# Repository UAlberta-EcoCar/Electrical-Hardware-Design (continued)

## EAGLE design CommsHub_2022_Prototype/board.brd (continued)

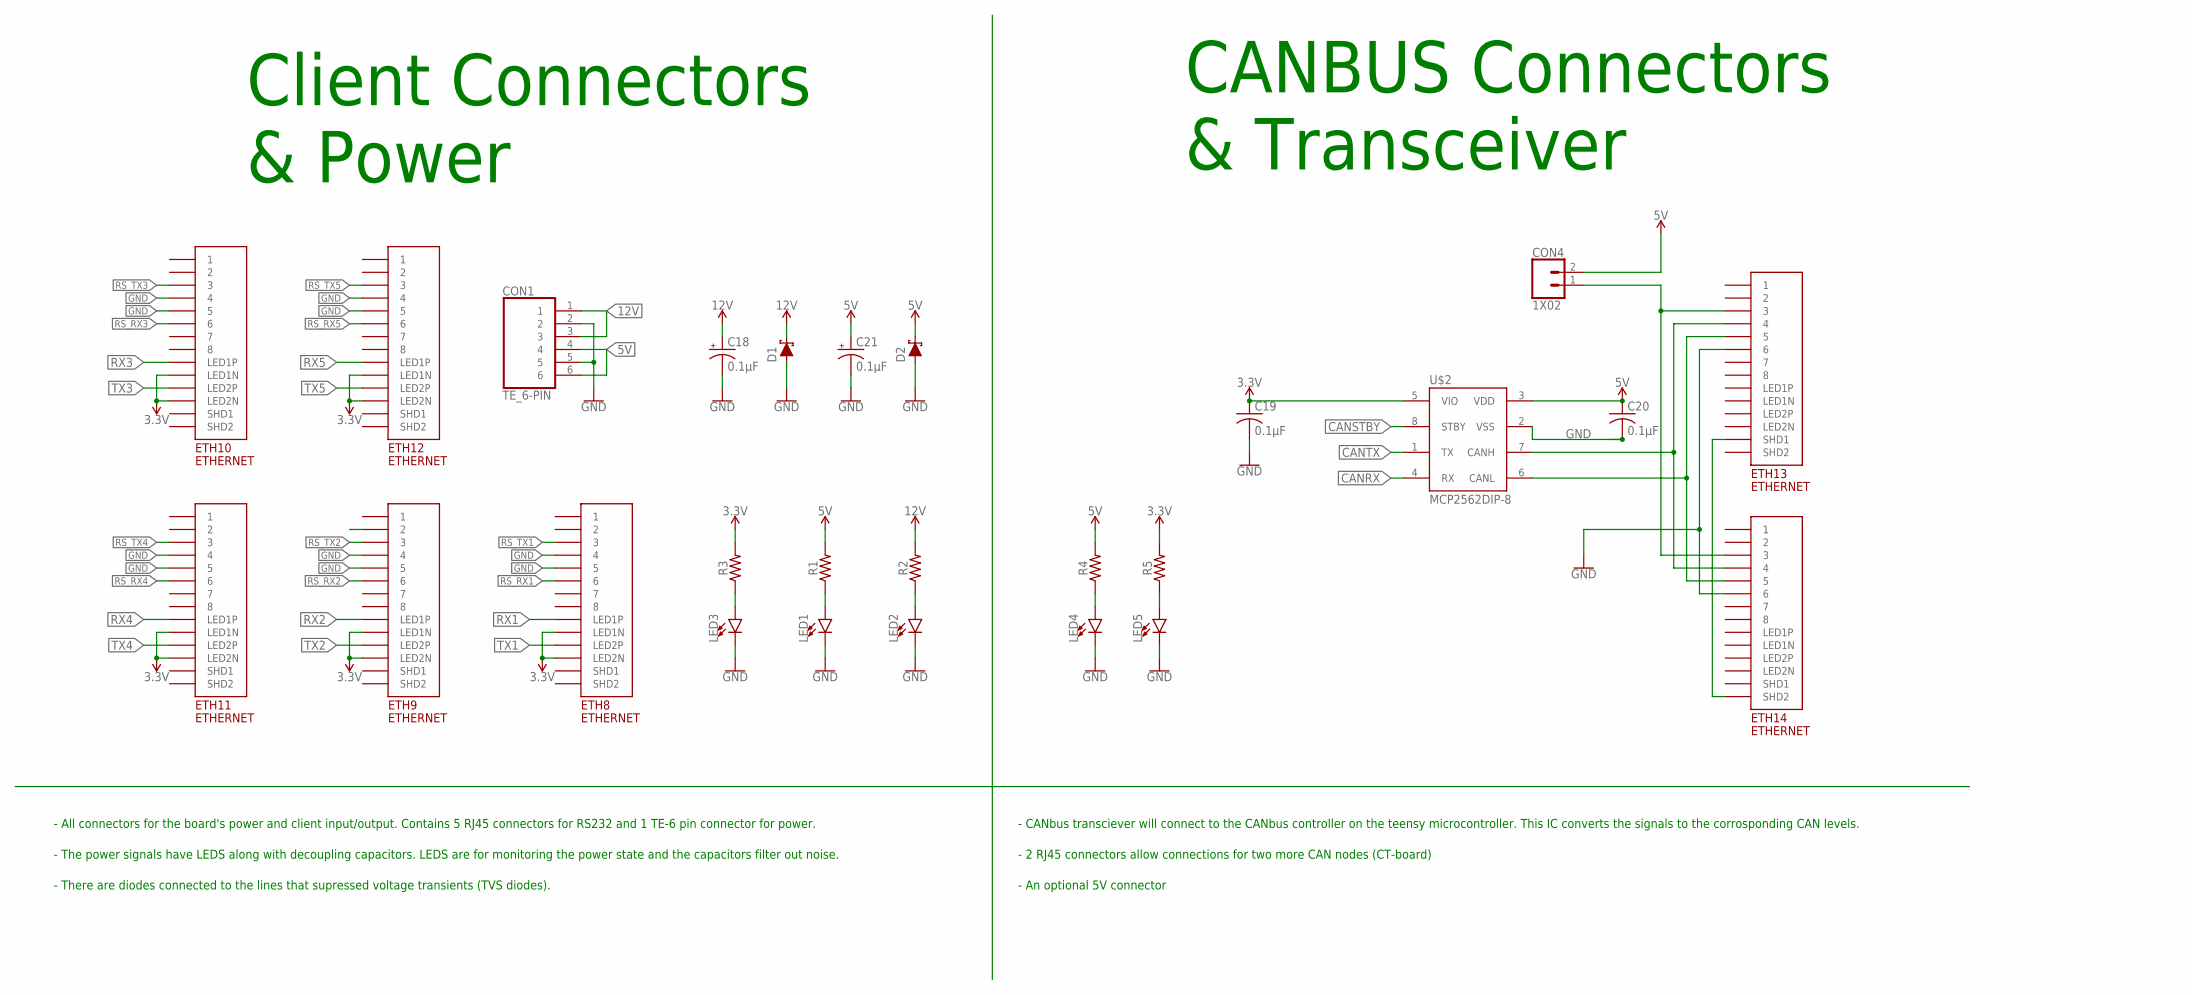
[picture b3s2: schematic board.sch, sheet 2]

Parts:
C18, C21: 0.1µF; CAPACITOR_100UF_50V
C19, C20: 0.1µF; C0805
CON1: TE_6-PIN
CON4: 1X02
D1, D2: DIODE_SCHOTTKY_DO-214AA; DO214AA
ETH8, ETH9, ETH10, ETH11, ETH12, ETH13, ETH14: ETHERNET; A122645-ND
LED1, LED2, LED3, LED4, LED5: LED_0805; 0805_LED
R1, R2, R3, R4, R5: RESISTOR_0805; 0805
U$2: MCP2562DIP-8; DIL08

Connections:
3.3V: C19.1, ETH8.P$9 (LED1N), ETH8.P$11 (LED2N), ETH9.P$9 (LED1N), ETH9.P$11 (LED2N), ETH10.P$9 (LED1N), ETH10.P$11 (LED2N), ETH11.P$9 (LED1N), ETH11.P$11 (LED2N), ETH12.P$9 (LED1N), ETH12.P$11 (LED2N), R3.2, R5.2, U$2.5 (VIO); also elsewhere on the board
5V: C20.1, C21.+, CON1.4, CON1.6, CON4.2, D2.C, R1.2, R4.2, U$2.3 (VDD)
12V: C18.+, CON1.1, CON1.3, D1.C, R2.2
CANRX: U$2.4 (RX); also elsewhere on the board
CANSTBY: U$2.8 (STBY); also elsewhere on the board
CANTX: U$2.1 (TX); also elsewhere on the board
GND: C18.-, C19.2, C20.2, C21.-, CON1.2, CON1.5, D1.A, D2.A, ETH8.P$4 (4), ETH8.P$5 (5), ETH9.P$4 (4), ETH9.P$5 (5), ETH10.P$4 (4), ETH10.P$5 (5), ETH11.P$4 (4), ETH11.P$5 (5), ETH12.P$4 (4), ETH12.P$5 (5), ETH13.P$6 (6), ETH14.P$6 (6), LED1.2 (C), LED2.2 (C), LED3.2 (C), LED4.2 (C), LED5.2 (C), U$2.2 (VSS); also elsewhere on the board
unnamed: ETH13.P$4 (4), ETH14.P$4 (4), U$2.7 (CANH)
unnamed: ETH13.P$5 (5), ETH14.P$5 (5), U$2.6 (CANL)
unnamed: CON4.1, ETH13.P$3 (3), ETH14.P$3 (3)
unnamed: ETH13.P$13 (SHD1), ETH14.P$14 (SHD2)
unnamed: LED2.1 (A), R2.1
unnamed: LED1.1 (A), R1.1
unnamed: LED3.1 (A), R3.1
unnamed: LED4.1 (A), R4.1
unnamed: LED5.1 (A), R5.1
RS_RX1: ETH8.P$6 (6); also elsewhere on the board
RS_RX2: ETH9.P$6 (6); also elsewhere on the board
RS_RX3: ETH10.P$6 (6); also elsewhere on the board
RS_RX4: ETH11.P$6 (6); also elsewhere on the board
RS_RX5: ETH12.P$6 (6); also elsewhere on the board
RS_TX1: ETH8.P$3 (3); also elsewhere on the board
RS_TX2: ETH9.P$3 (3); also elsewhere on the board
RS_TX3: ETH10.P$3 (3); also elsewhere on the board
RS_TX4: ETH11.P$3 (3); also elsewhere on the board
RS_TX5: ETH12.P$3 (3); also elsewhere on the board
RX1: ETH8.P$10 (LED1P); also elsewhere on the board
RX2: ETH9.P$10 (LED1P); also elsewhere on the board
RX3: ETH10.P$10 (LED1P); also elsewhere on the board
RX4: ETH11.P$10 (LED1P); also elsewhere on the board
RX5: ETH12.P$10 (LED1P); also elsewhere on the board
TX1: ETH8.P$12 (LED2P); also elsewhere on the board
TX2: ETH9.P$12 (LED2P); also elsewhere on the board
TX3: ETH10.P$12 (LED2P); also elsewhere on the board
TX4: ETH11.P$12 (LED2P); also elsewhere on the board
TX5: ETH12.P$12 (LED2P); also elsewhere on the board

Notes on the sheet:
Client Connectors & Power
CANBUS Connectors & Transceiver
- All connectors for the board's power and client input/output. Contains 5 RJ45 connectors for RS232 and 1 TE-6 pin connector for power. - The power signals have LEDS along with decoupling capacitors. LEDS are for monitoring the power state and the capacitors filter out noise. - There are diodes co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
- CANbus transciever will connect to the CANbus controller on the teensy microcontroller. This IC converts the signals to the corrosponding CAN levels. - 2 RJ45 connectors allow connections for two more CAN nodes (CT-board) - An optional 5V connector

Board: 2 copper layers, 46 parts (0 on the bottom side), 55 nets, no tracks yet.

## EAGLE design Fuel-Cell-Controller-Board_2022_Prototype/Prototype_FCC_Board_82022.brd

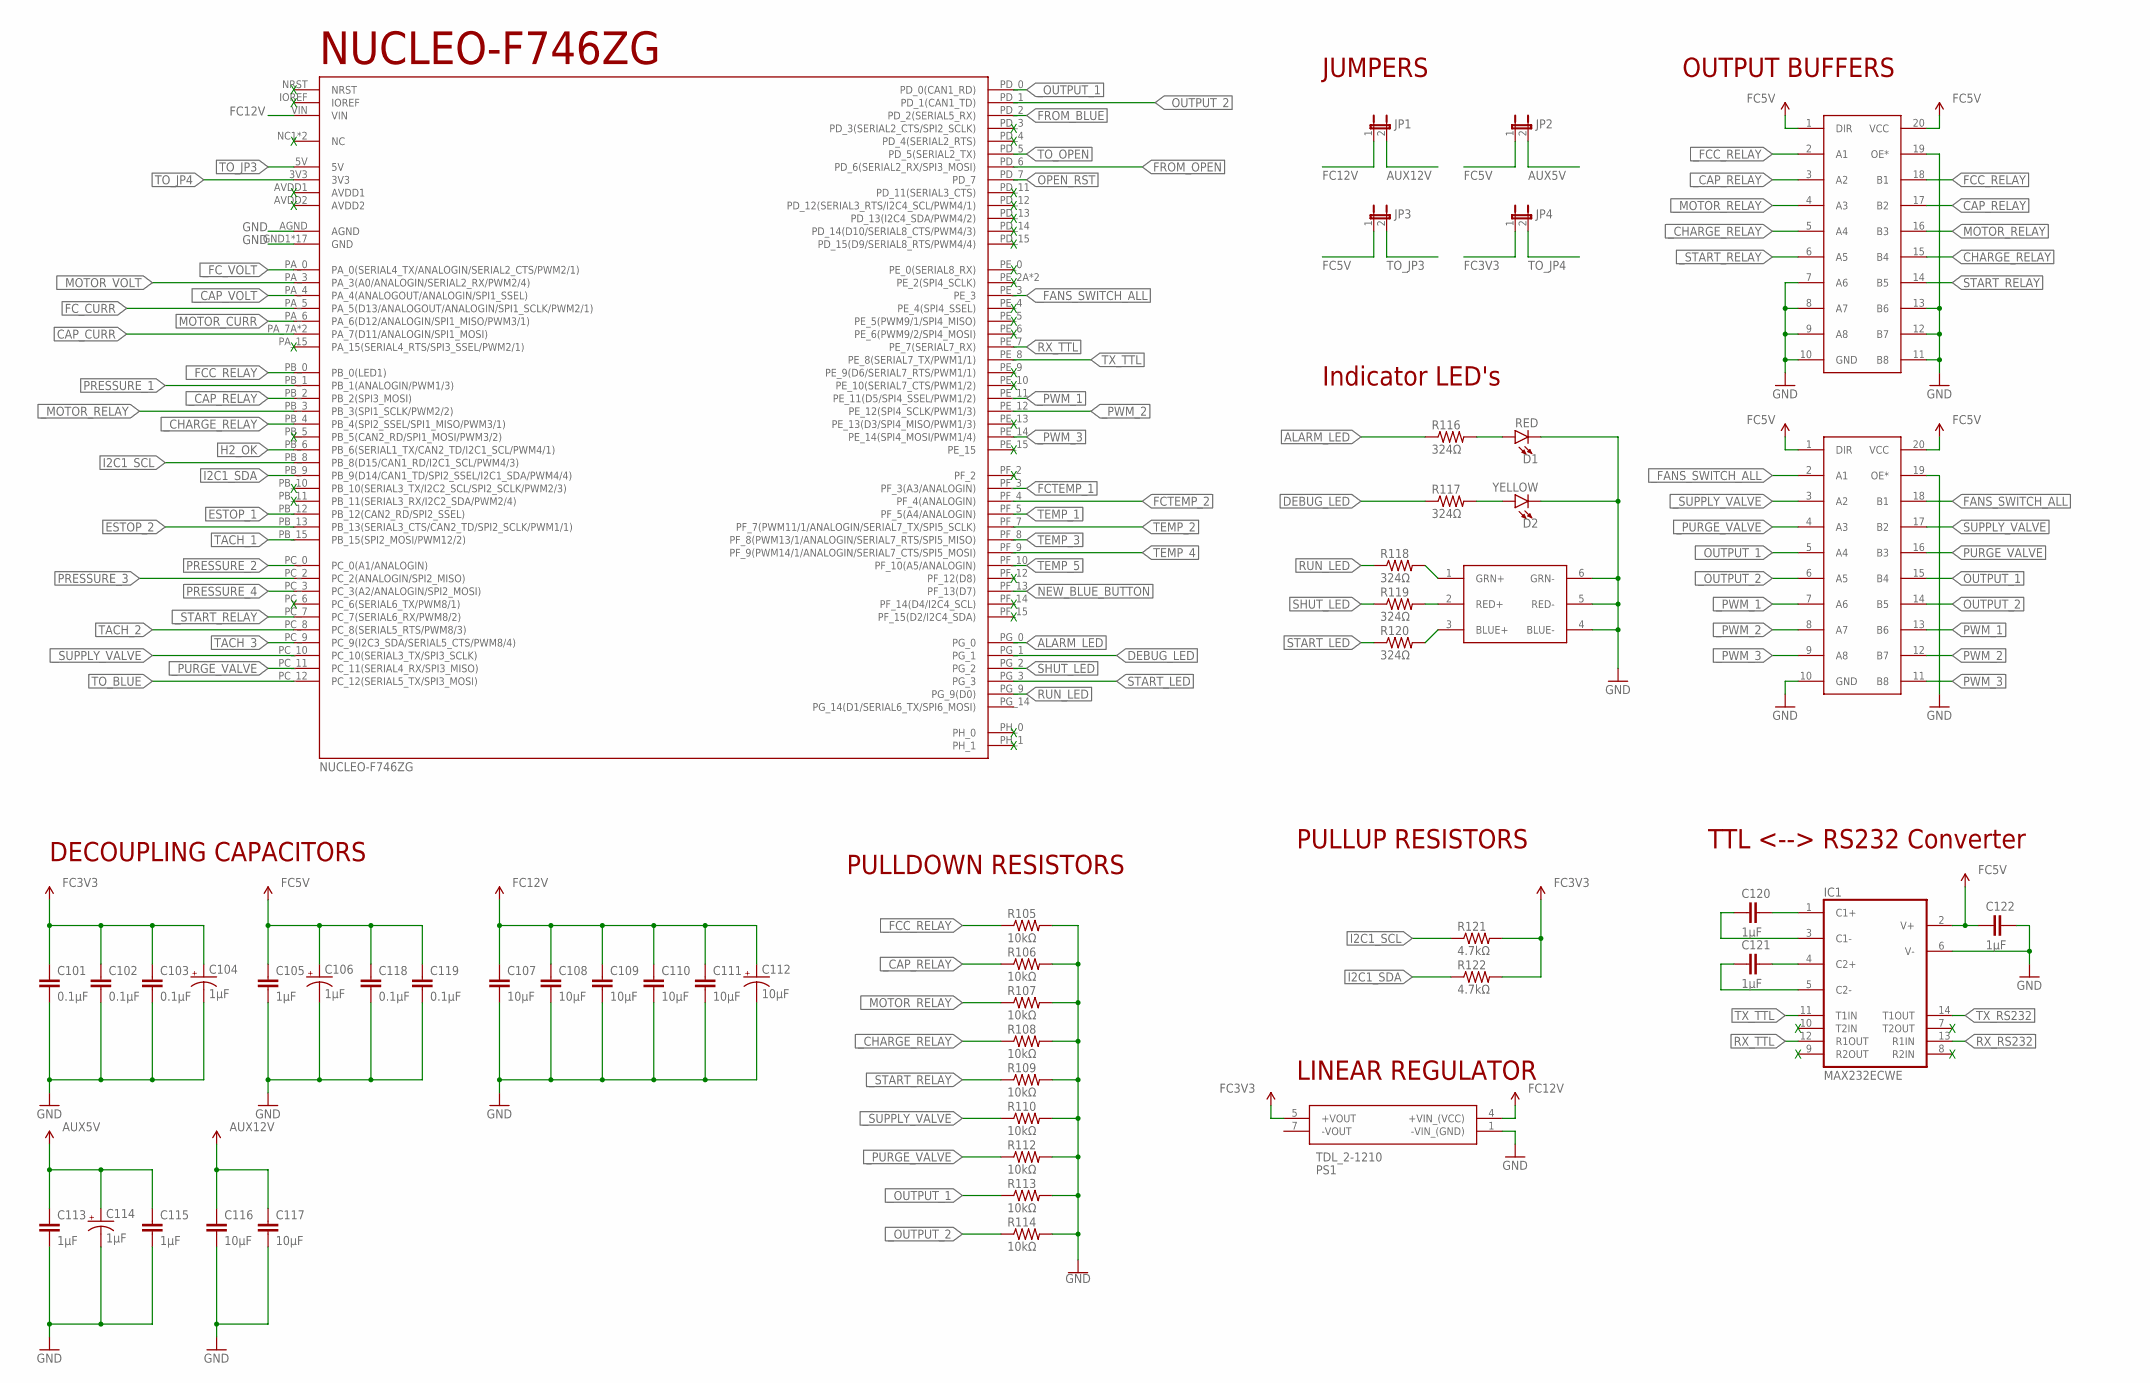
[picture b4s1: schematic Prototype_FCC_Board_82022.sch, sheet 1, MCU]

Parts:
C101, C102, C103, C118, C119: 0.1µF; 0805
C104, C106, C114: 1µF; PANASONIC_D
C105, C113, C115, C120, C121, C122: 1µF; 0805
C107, C108, C109, C110, C111, C116, C117: 10µF; 0805
C112: 10µF; PANASONIC_D
D1: RED; LED-1206
D2: YELLOW; LED-1206
IC1: MAX232ECWE; SO16L
JP1, JP2, JP3, JP4: JP1E; JP1
PS1: TDL_2-1210; TDL21210
R105, R106, R107, R108, R109, R110, R112, R113, R114: 10kΩ; 0805
R116, R117, R118, R119, R120: 324Ω; 0805
R121, R122: 4.7kΩ; 0805
U$1: NUCLEO-F746ZGNUCLEO-F746ZG; NUCLEO-F746ZG
U$3, U$5: SN74LVC245AN; DIL20
U$25: 5060BRG45060BRG4; 5060BRG4

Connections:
ALARM_LED: R116.1, U$1.PG_0
AUX5V: C113.1, C114.+, C115.1, JP2.2; also elsewhere on the board
AUX12V: C116.1, C117.1, JP1.2; also elsewhere on the board
CAP_CURR: U$1.PA_7A (PA_7(D11/ANALOGIN/SPI1_MOSI)), U$1.PA_7B (PA_7(D11/ANALOGIN/SPI1_MOSI)); also elsewhere on the board
CAP_RELAY: U$5.17 (B2); also elsewhere on the board
CHARGE_RELAY: U$5.15 (B4); also elsewhere on the board
DEBUG_LED: R117.1, U$1.PG_1
ESTOP_1: U$1.PB_12 (PB_12(CAN2_RD/SPI2_SSEL)); also elsewhere on the board
ESTOP_2: U$1.PB_13 (PB_13(SERIAL3_CTS/CAN2_TD/SPI2_SCLK/PWM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); also elsewhere on the board
FANS_SWITCH_ALL: U$3.18 (B1); also elsewhere on the board
FC12V: C107.1, C108.1, C109.1, C110.1, C111.1, C112.+, JP1.1, PS1.4 (+VIN_(VCC)), U$1.VIN; also elsewhere on the board
FCC_RELAY: U$5.18 (B1); also elsewhere on the board
FCTEMP_1: U$1.PF_3 (PF_3(A3/ANALOGIN)); also elsewhere on the board
FCTEMP_2: U$1.PF_4 (PF_4(ANALOGIN)); also elsewhere on the board
FC_CURR: U$1.PA_5 (PA_5(D13/ANALOGOUT/ANALOGIN/SPI1_SCLK/P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); also elsewhere on the board
FROM_BLUE: U$1.PD_2 (PD_2(SERIAL5_RX)); also elsewhere on the board
FROM_OPEN: U$1.PD_6 (PD_6(SERIAL2_RX/SPI3_MOSI)); also elsewhere on the board
GND: C101.2, C102.2, C103.2, C104.-, C105.2, C106.-, C107.2, C108.2, C109.2, C110.2, C111.2, C112.-, C113.2, C114.-, C115.2, C116.2, C117.2, C118.2, C119.2, C122.1, D1.C, D2.C, IC1.6 (V-), IC1.15 (GND), PS1.1 (-VIN_(GND)), R105.2, R106.2, R107.2, R108.2, R109.2, R110.2, R112.2, R113.2, R114.2, U$1.AGND, U$1.GND1 (GND), U$1.GND2 (GND), U$1.GND3 (GND), U$1.GND4 (GND), U$1.GND5 (GND), U$1.GND6 (GND), U$1.GND7 (GND), U$1.GND8 (GND), U$1.GND9 (GND), U$1.GND10 (GND), U$1.GND11 (GND), U$1.GND12 (GND), U$1.GND13 (GND), U$1.GND14 (GND), U$1.GND15 (GND), U$1.GND16 (GND), U$1.GND17 (GND), U$3.10 (GND), U$3.19 (OE*), U$5.7 (A6), U$5.8 (A7), U$5.9 (A8), U$5.10 (GND), U$5.11 (B8), U$5.12 (B7), U$5.13 (B6), U$5.19 (OE*), U$25.4 (BLUE-), U$25.5 (RED-), U$25.6 (GRN-); also elsewhere on the board
H2_OK: U$1.PB_6 (PB_6(SERIAL1_TX/CAN2_TD/I2C1_SCL/PWM4/1)); also elsewhere on the board
I2C1_SCL: R121.1, U$1.PB_8 (PB_8(D15/CAN1_RD/I2C1_SCL/PWM4/3)); also elsewhere on the board
I2C1_SDA: R122.1, U$1.PB_9 (PB_9(D14/CAN1_TD/SPI2_SSEL/I2C1_SDA/PWM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); also elsewhere on the board
MOTOR_CURR: U$1.PA_6 (PA_6(D12/ANALOGIN/SPI1_MISO/PWM3/1)); also elsewhere on the board
MOTOR_RELAY: U$5.16 (B3); also elsewhere on the board
unnamed: D1.A, R116.2
unnamed: D2.A, R117.2
unnamed: R118.2, U$25.1 (GRN+)
unnamed: R119.2, U$25.2 (RED+)
unnamed: R120.2, U$25.3 (BLUE+)
unnamed: C120.1, IC1.1 (C1+)
unnamed: C120.2, IC1.3 (C1-)
unnamed: C121.2, IC1.4 (C2+)
unnamed: C121.1, IC1.5 (C2-)
NEW_BLUE_BUTTON: U$1.PF_13 (PF_13(D7))
OPEN_RST: U$1.PD_7; also elsewhere on the board
OUTPUT_1: U$3.15 (B4); also elsewhere on the board
OUTPUT_2: U$3.14 (B5); also elsewhere on the board
PRESSURE_1: U$1.PB_1 (PB_1(ANALOGIN/PWM1/3)); also elsewhere on the board
PRESSURE_2: U$1.PC_0 (PC_0(A1/ANALOGIN)); also elsewhere on the board
PRESSURE_3: U$1.PC_2 (PC_2(ANALOGIN/SPI2_MISO)); also elsewhere on the board
PRESSURE_4: U$1.PC_3 (PC_3(A2/ANALOGIN/SPI2_MOSI)); also elsewhere on the board
PURGE_VALVE: U$3.16 (B3); also elsewhere on the board
PWM_1: U$3.13 (B6); also elsewhere on the board
PWM_2: U$3.12 (B7); also elsewhere on the board
PWM_3: U$3.11 (B8); also elsewhere on the board
RUN_LED: R118.1, U$1.PG_9 (PG_9(D0))
RX_RS232: IC1.13 (R1IN); also elsewhere on the board
RX_TTL: IC1.12 (R1OUT), U$1.PE_7 (PE_7(SERIAL7_RX))
SHUT_LED: R119.1, U$1.PG_2
START_LED: R120.1, U$1.PG_3
START_RELAY: U$5.14 (B5); also elsewhere on the board
SUPPLY_VALVE: U$3.17 (B2); also elsewhere on the board
TACH_1: U$1.PB_15 (PB_15(SPI2_MOSI/PWM12/2)); also elsewhere on the board
TACH_2: U$1.PC_8 (PC_8(SERIAL5_RTS/PWM8/3)); also elsewhere on the board
TACH_3: U$1.PC_9 (PC_9(I2C3_SDA/SERIAL5_CTS/PWM8/4)); also elsewhere on the board
TEMP_1: U$1.PF_5 (PF_5(A4/ANALOGIN)); also elsewhere on the board
TEMP_2: U$1.PF_7 (PF_7(PWM11/1/ANALOGIN/SERIAL7_TX/SPI5_S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); also elsewhere on the board
TEMP_3: U$1.PF_8 (PF_8(PWM13/1/ANALOGIN/SERIAL7_RTS/SPI5_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); also elsewhere on the board
TEMP_4: U$1.PF_9 (PF_9(PWM14/1/ANALOGIN/SERIAL7_CTS/SPI5_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); also elsewhere on the board
TEMP_5: U$1.PF_10 (PF_10(A5/ANALOGIN)); also elsewhere on the board
TO_BLUE: U$1.PC_12 (PC_12(SERIAL5_TX/SPI3_MOSI)); also elsewhere on the board
TO_JP3: JP3.2, U$1.5V
TO_JP4: JP4.2, U$1.3V3
TO_OPEN: U$1.PD_5 (PD_5(SERIAL2_TX)); also elsewhere on the board
TX_RS232: IC1.14 (T1OUT); also elsewhere on the board
TX_TTL: IC1.11 (T1IN), U$1.PE_8 (PE_8(SERIAL7_TX/PWM1/1))
VCC: IC1.16 (VCC)
_CAP_RELAY: R106.1, U$1.PB_2 (PB_2(SPI3_MOSI)), U$5.3 (A2)
_CAP_VOLT: U$1.PA_4 (PA_4(ANALOGOUT/ANALOGIN/SPI1_SSEL)); also elsewhere on the board
_CHARGE_RELAY: R108.1, U$1.PB_4 (PB_4(SPI2_SSEL/SPI1_MISO/PWM3/1)), U$5.5 (A4)
_FANS_SWITCH_ALL: U$1.PE_3, U$3.2 (A1)
_FCC_RELAY: R105.1, U$1.PB_0 (PB_0(LED1)), U$5.2 (A1)
_FC_VOLT: U$1.PA_0 (PA_0(SERIAL4_TX/ANALOGIN/SERIAL2_CTS/PW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); also elsewhere on the board
_MOTOR_RELAY: R107.1, U$1.PB_3 (PB_3(SPI1_SCLK/PWM2/2)), U$5.4 (A3)
_MOTOR_VOLT: U$1.PA_3 (PA_3(A0/ANALOGIN/SERIAL2_RX/PWM2/4)); also elsewhere on the board
_OUTPUT_1: R113.1, U$1.PD_0 (PD_0(CAN1_RD)), U$3.5 (A4)
_OUTPUT_2: R114.1, U$1.PD_1 (PD_1(CAN1_TD)), U$3.6 (A5)
_PURGE_VALVE: R112.1, U$1.PC_11 (PC_11(SERIAL4_RX/SPI3_MISO)), U$3.4 (A3)
_PWM_1: U$1.PE_11 (PE_11(D5/SPI4_SSEL/PWM1/2)), U$3.7 (A6)
_PWM_2: U$1.PE_12 (PE_12(SPI4_SCLK/PWM1/3)), U$3.8 (A7)
_PWM_3: U$1.PE_14 (PE_14(SPI4_MOSI/PWM1/4)), U$3.9 (A8)
_START_RELAY: R109.1, U$1.PC_7 (PC_7(SERIAL6_RX/PWM8/2)), U$5.6 (A5)
_SUPPLY_VALVE: R110.1, U$1.PC_10 (PC_10(SERIAL3_TX/SPI3_SCLK)), U$3.3 (A2)

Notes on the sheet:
NUCLEO-F746ZG
OUTPUT BUFFERS
Indicator LED's
DECOUPLING CAPACITORS
JUMPERS
PULLDOWN RESISTORS
TTL <--> RS232 Converter
PULLUP RESISTORS
LINEAR REGULATOR

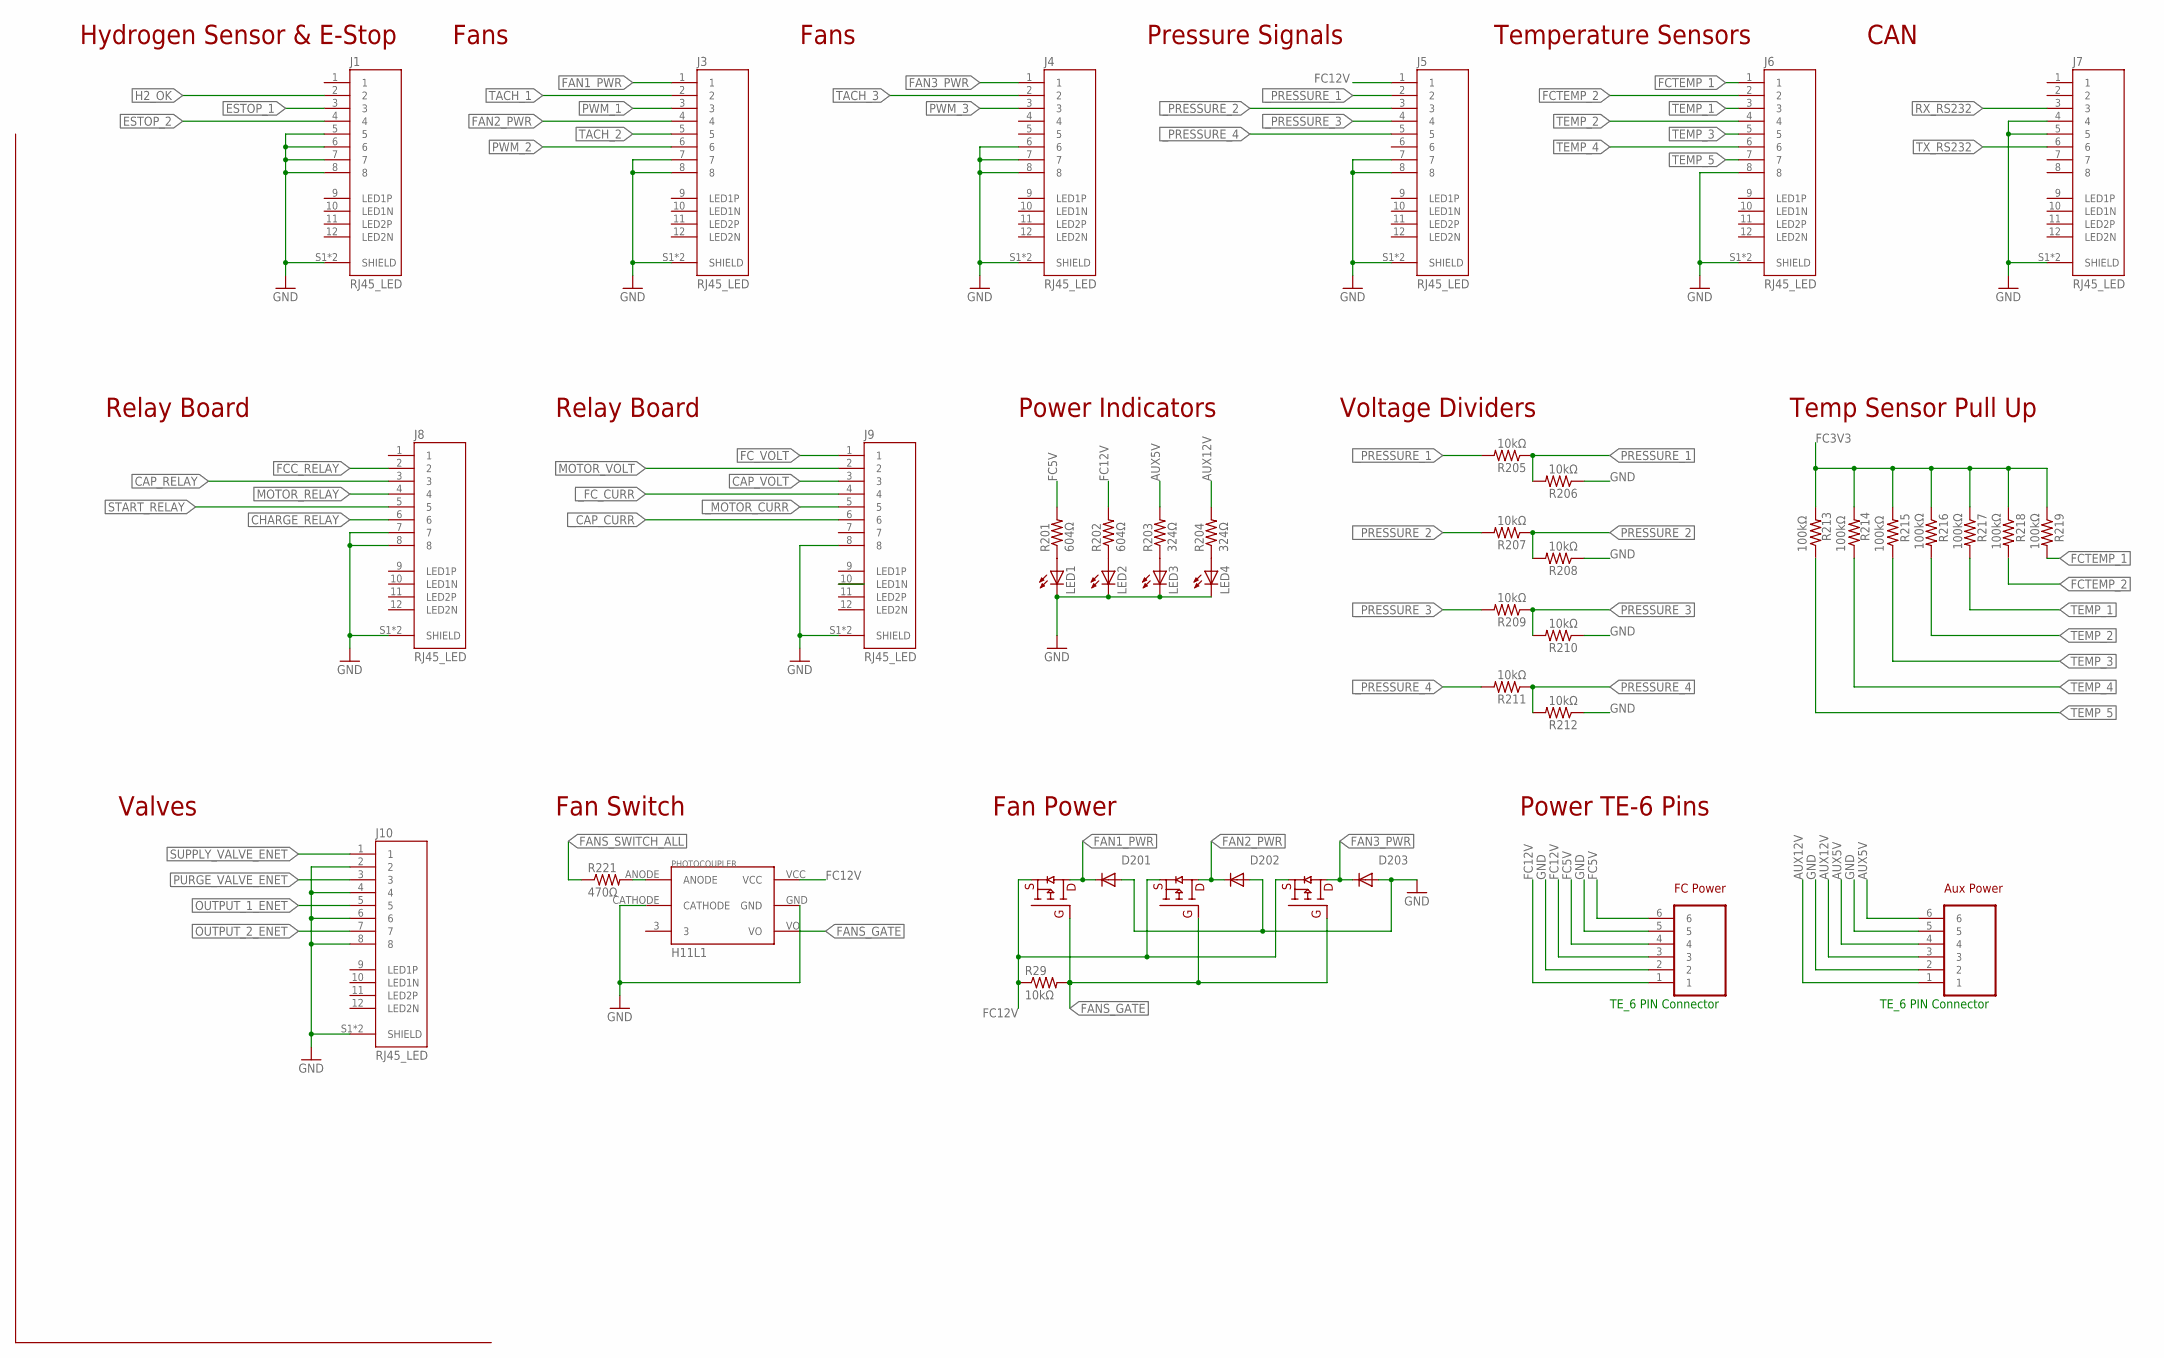
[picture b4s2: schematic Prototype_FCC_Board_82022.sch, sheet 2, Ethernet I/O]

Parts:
AUX_PWR1: TE_6-PIN
D201, D202, D203: DIODE-DO214AC; DO214AC
FC_PWR1: TE_6-PIN
J1, J3, J4, J5, J6, J7, J8, J9, J10: RJ45_LED
LED1, LED2, LED3, LED4: LEDCHIP-LED0805; CHIP-LED0805
R29, R205, R206, R207, R208, R209, R210, R211, R212: 10kΩ; 0805
R201, R202: 604Ω; R0805
R203, R204: 324Ω; R0805
R213, R214, R215, R216, R217, R218, R219: 100kΩ; 0805
R221: 470Ω; 0805
U$10: H11L1H11L1; H11L1
U$19, U$23, U$24: DMP3056L-7DMP3056L-7; DMP3056L-7

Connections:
AUX5V: AUX_PWR1.4, AUX_PWR1.6, R203.2; also elsewhere on the board
AUX12V: AUX_PWR1.1, AUX_PWR1.3, R204.2; also elsewhere on the board
CAP_RELAY: J8.3; also elsewhere on the board
CAP_VOLT: J9.3; also elsewhere on the board
CHARGE_RELAY: J8.6; also elsewhere on the board
ESTOP_1: J1.3; also elsewhere on the board
ESTOP_2: J1.4; also elsewhere on the board
FAN1_PWR: D201.C, J3.1, U$19.D (DRAIN)
FAN2_PWR: D202.C, J3.4, U$23.D (DRAIN)
FAN3_PWR: D203.C, J4.1, U$24.D (DRAIN)
FANS_GATE: R29.2, U$10.VO, U$19.G (GATE), U$23.G (GATE), U$24.G (GATE)
FANS_SWITCH_ALL: R221.1; also elsewhere on the board
FC12V: FC_PWR1.1, FC_PWR1.3, J5.1, R29.1, R202.2, U$10.VCC, U$19.S (SOURCE), U$23.S (SOURCE), U$24.S (SOURCE); also elsewhere on the board
FCC_RELAY: J8.2; also elsewhere on the board
FCTEMP_1: J6.1, R219.2; also elsewhere on the board
FCTEMP_2: J6.2, R218.2; also elsewhere on the board
FC_VOLT: J9.1; also elsewhere on the board
GND: AUX_PWR1.2, AUX_PWR1.5, D201.A, D202.A, D203.A, FC_PWR1.2, FC_PWR1.5, J1.5, J1.6, J1.7, J1.8, J1.S1 (SHIELD), J1.S2 (SHIELD), J3.7, J3.8, J3.S1 (SHIELD), J3.S2 (SHIELD), J4.6, J4.7, J4.8, J4.S1 (SHIELD), J4.S2 (SHIELD), J5.7, J5.8, J5.S1 (SHIELD), J5.S2 (SHIELD), J6.8, J6.S1 (SHIELD), J6.S2 (SHIELD), J7.4, J7.5, J7.S1 (SHIELD), J7.S2 (SHIELD), J8.7, J8.8, J8.S1 (SHIELD), J8.S2 (SHIELD), J9.8, J9.S1 (SHIELD), J9.S2 (SHIELD), J10.2, J10.4, J10.6, J10.8, J10.S1 (SHIELD), J10.S2 (SHIELD), LED1.C, LED2.C, LED3.C, LED4.C, R206.1, R208.1, R210.1, R212.1, U$10.CATHODE, U$10.GND; also elsewhere on the board
H2_OK: J1.2; also elsewhere on the board
MOTOR_RELAY: J8.4; also elsewhere on the board
MOTOR_VOLT: J9.2; also elsewhere on the board
unnamed: LED1.A, R201.1
unnamed: LED2.A, R202.1
unnamed: LED3.A, R203.1
unnamed: LED4.A, R204.1
unnamed: R221.2, U$10.ANODE
OUTPUT_1_ENET: J10.5; also elsewhere on the board
OUTPUT_2_ENET: J10.7; also elsewhere on the board
PRESSURE_1: R205.1, R206.2; also elsewhere on the board
PRESSURE_2: R207.1, R208.2; also elsewhere on the board
PRESSURE_3: R209.1, R210.2; also elsewhere on the board
PRESSURE_4: R211.1, R212.2; also elsewhere on the board
PURGE_VALVE_ENET: J10.3; also elsewhere on the board
PWM_1: J3.3; also elsewhere on the board
PWM_2: J3.6; also elsewhere on the board
PWM_3: J4.3; also elsewhere on the board
RX_RS232: J7.3; also elsewhere on the board
START_RELAY: J8.5; also elsewhere on the board
SUPPLY_VALVE_ENET: J10.1; also elsewhere on the board
TACH_1: J3.2; also elsewhere on the board
TACH_2: J3.5; also elsewhere on the board
TACH_3: J4.2; also elsewhere on the board
TEMP_1: J6.3, R217.2; also elsewhere on the board
TEMP_2: J6.4, R216.2; also elsewhere on the board
TEMP_3: J6.5, R215.1; also elsewhere on the board
TEMP_4: J6.6, R214.1; also elsewhere on the board
TEMP_5: J6.7, R213.1; also elsewhere on the board
TX_RS232: J7.6; also elsewhere on the board
_CAP_CURR: J9.6; also elsewhere on the board
_FC_CURR: J9.4; also elsewhere on the board
_MOTOR_CURR: J9.5; also elsewhere on the board
_PRESSURE_1: J5.2, R205.2
_PRESSURE_2: J5.3, R207.2
_PRESSURE_3: J5.4, R209.2
_PRESSURE_4: J5.5, R211.2

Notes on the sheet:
FC Power
Aux Power
TE_6 PIN Connector
Hydrogen Sensor & E-Stop
Fans
Pressure Signals
Temperature Sensors
Relay Board
Power Indicators
Voltage Dividers
Temp Sensor Pull Up
Valves
Fan Switch
Fan Power
Power TE-6 Pins
CAN

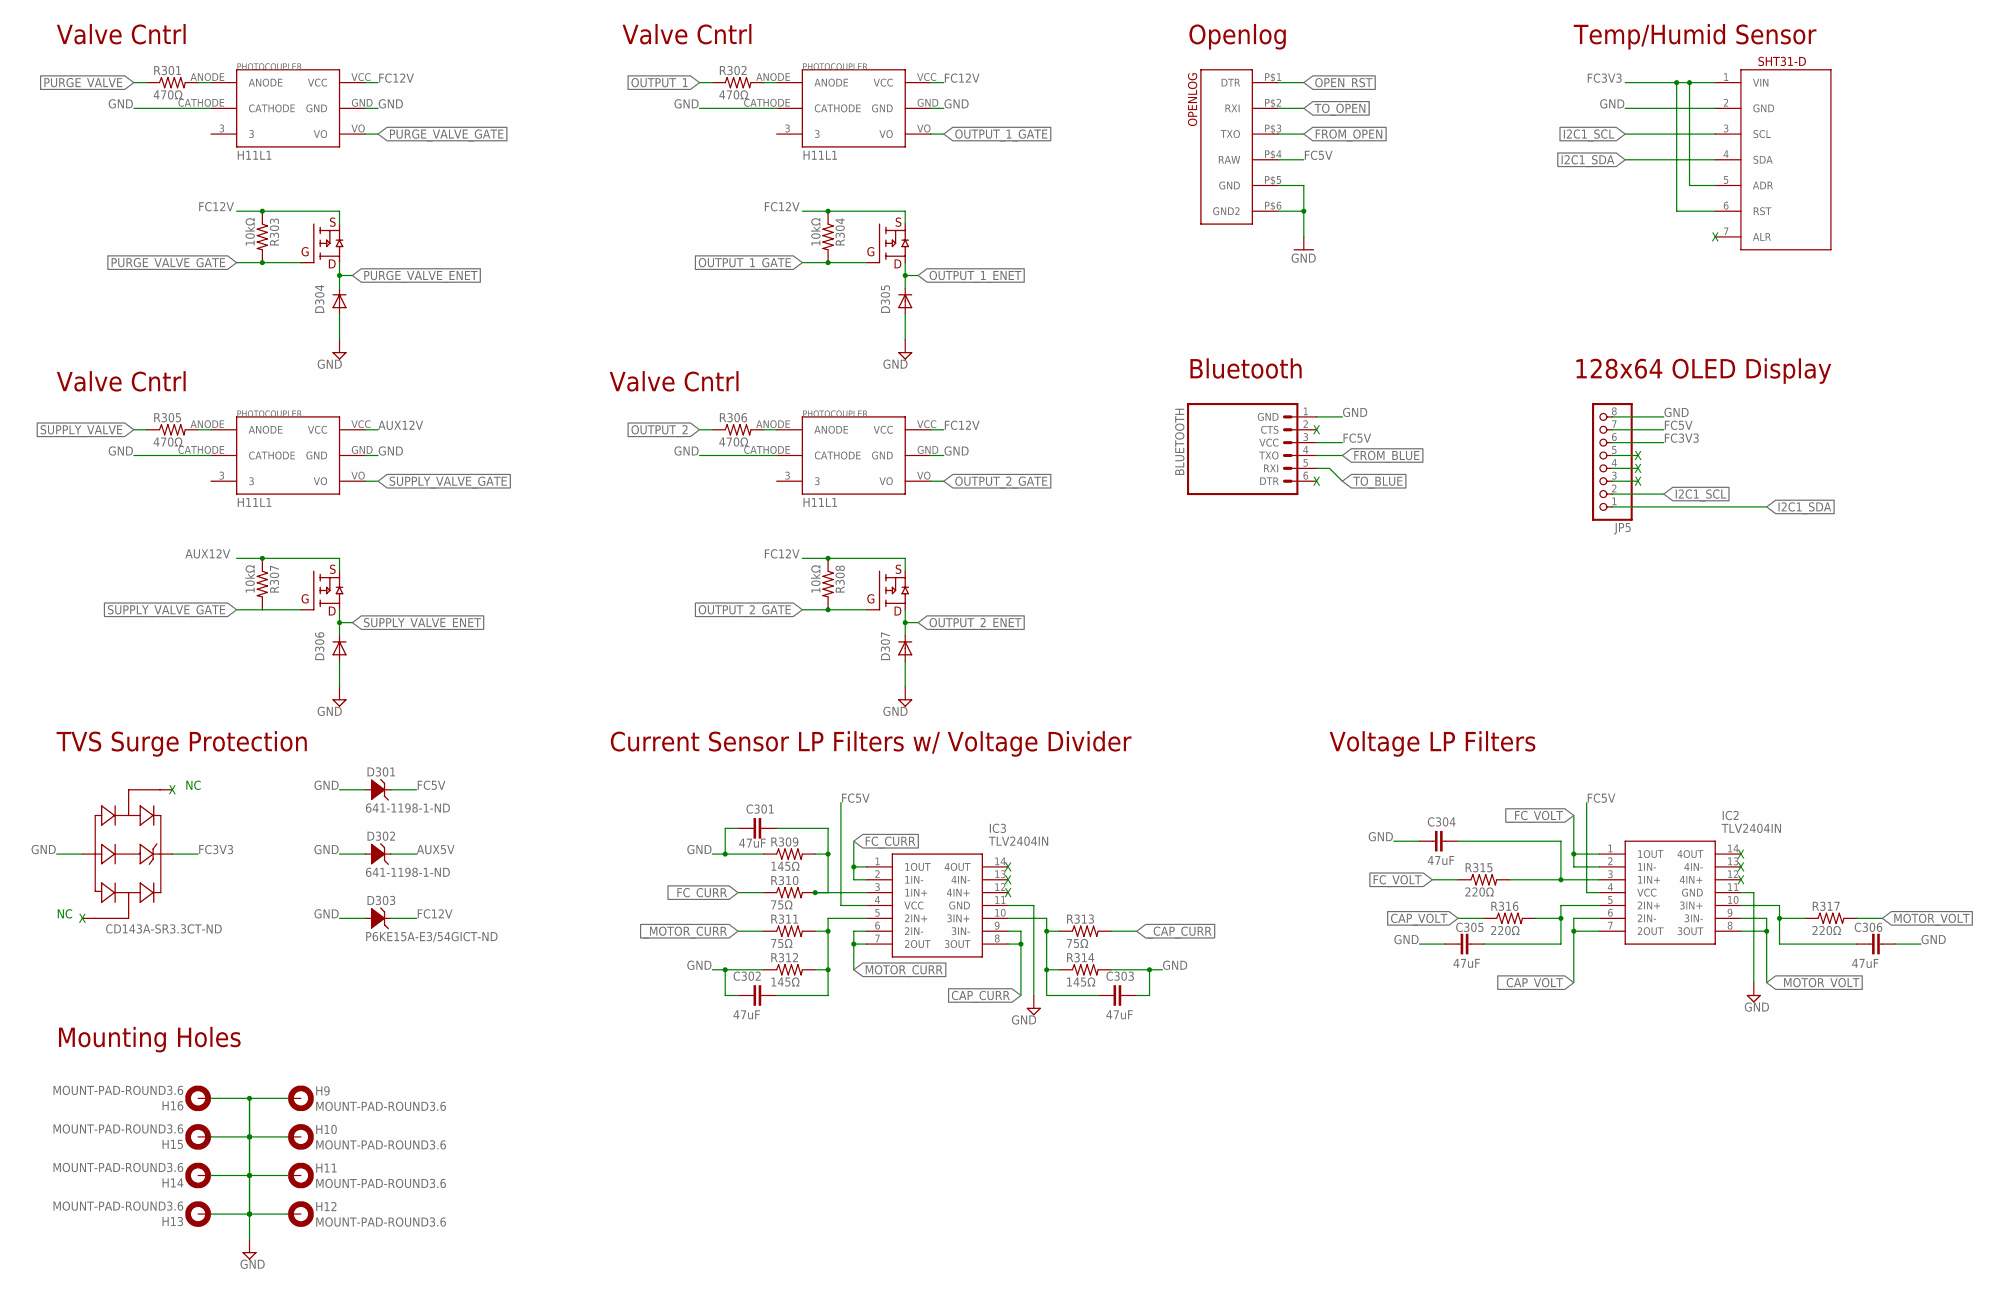
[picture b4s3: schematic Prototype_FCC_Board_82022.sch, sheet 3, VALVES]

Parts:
C301, C302, C303, C304, C305, C306: 47uF; 0805
D301, D302: 641-1198-1-ND; SOT23
D303: P6KE15A-E3/54GICT-ND; DO-204AC
D304, D305, D306, D307: DIODE-DO214AC; DO214AC
H9, H10, H11, H12, H13, H14, H15, H16: MOUNT-PAD-ROUND3.6; 3,6-PAD
IC2, IC3: TLV2404IN; DIP794W53P254L1930H508Q14N
J2: BLUETOOTH; 1X06BLUETOOTH
JP5: PINHD-1X8CLEANBIG; 1X08-CLEANBIG
R301, R302, R305, R306: 470Ω; 0805
R303, R304, R307, R308: 10kΩ; 0805
R309, R312, R314: 145Ω; R0805
R310, R311, R313: 75Ω; R0805
R315, R316, R317: 220Ω; R0805
SHTSENSOR1: SHT31-DIS; 1X07-SHT31-DIS
U$4: OPENLOG
U$6, U$11, U$14, U$16: H11L1H11L1; H11L1
U$8: CD143A-SR3.3CT-ND; SOT143_AVAGO
U$12, U$13, U$15, U$17: DMP3056L-7DMP3056L-7; DMP3056L-7

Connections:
AUX5V: D302.C; also elsewhere on the board
AUX12V: R307.1, U$6.VCC, U$12.S (SOURCE); also elsewhere on the board
CAP_CURR: IC3.8 (3OUT), IC3.9 (3IN-); also elsewhere on the board
CAP_VOLT: R316.1; also elsewhere on the board
FC12V: D303.CATHODE (C), R303.1, R304.1, R308.1, U$11.VCC, U$13.S (SOURCE), U$14.VCC, U$15.S (SOURCE), U$16.VCC, U$17.S (SOURCE); also elsewhere on the board
FC_CURR: IC3.1 (1OUT), IC3.2 (1IN-); also elsewhere on the board
FC_VOLT: R315.1; also elsewhere on the board
FROM_BLUE: J2.4 (TXO); also elsewhere on the board
FROM_OPEN: U$4.P$3 (TXO); also elsewhere on the board
GND: C301.1, C302.1, C303.2, C304.2, C305.2, C306.1, D301.A1 (A), D301.A2 (A), D302.A1 (A), D302.A2 (A), D303.ANODE (A), D304.A, D305.A, D306.A, D307.A, H9.B3,6, H10.B3,6, H11.B3,6, H12.B3,6, H13.B3,6, H14.B3,6, H15.B3,6, H16.B3,6, IC2.11 (GND), IC3.11 (GND), J2.1 (GND), JP5.8, R309.1, R312.1, R314.2, SHTSENSOR1.2 (GND), U$4.P$5 (GND), U$4.P$6 (GND2), U$6.CATHODE, U$6.GND, U$8.GND, U$11.CATHODE, U$11.GND, U$14.CATHODE, U$14.GND, U$16.CATHODE, U$16.GND; also elsewhere on the board
I2C1_SCL: JP5.2, SHTSENSOR1.3 (SCL); also elsewhere on the board
I2C1_SDA: JP5.1, SHTSENSOR1.4 (SDA); also elsewhere on the board
MOTOR_CURR: IC3.6 (2IN-), IC3.7 (2OUT); also elsewhere on the board
MOTOR_VOLT: R317.2; also elsewhere on the board
unnamed: R305.2, U$6.ANODE
unnamed: C302.2, IC3.5 (2IN+), R311.2, R312.2
unnamed: R301.2, U$11.ANODE
unnamed: R302.2, U$14.ANODE
unnamed: R306.2, U$16.ANODE
unnamed: C303.1, IC3.10 (3IN+), R313.1, R314.1
unnamed: C301.2, IC3.3 (1IN+), R309.2, R310.2
unnamed: C304.1, IC2.3 (1IN+), R315.2
unnamed: C306.2, IC2.10 (3IN+), R317.1
unnamed: C305.1, IC2.5 (2IN+), R316.2
OPEN_RST: U$4.P$1 (DTR); also elsewhere on the board
OUTPUT_1: R302.1; also elsewhere on the board
OUTPUT_1_ENET: D305.C, U$15.D (DRAIN); also elsewhere on the board
OUTPUT_1_GATE: R304.2, U$14.VO, U$15.G (GATE)
OUTPUT_2: R306.1; also elsewhere on the board
OUTPUT_2_ENET: D307.C, U$17.D (DRAIN); also elsewhere on the board
OUTPUT_2_GATE: R308.2, U$16.VO, U$17.G (GATE)
PURGE_VALVE: R301.1; also elsewhere on the board
PURGE_VALVE_ENET: D304.C, U$13.D (DRAIN); also elsewhere on the board
PURGE_VALVE_GATE: R303.2, U$11.VO, U$13.G (GATE)
SUPPLY_VALVE: R305.1; also elsewhere on the board
SUPPLY_VALVE_ENET: D306.C, U$12.D (DRAIN); also elsewhere on the board
SUPPLY_VALVE_GATE: R307.2, U$6.VO, U$12.G (GATE)
TO_BLUE: J2.5 (RXI); also elsewhere on the board
TO_OPEN: U$4.P$2 (RXI); also elsewhere on the board
_CAP_CURR: R313.2; also elsewhere on the board
_CAP_VOLT: IC2.6 (2IN-), IC2.7 (2OUT); also elsewhere on the board
_FC_CURR: R310.1; also elsewhere on the board
_FC_VOLT: IC2.1 (1OUT), IC2.2 (1IN-); also elsewhere on the board
_MOTOR_CURR: R311.1; also elsewhere on the board
_MOTOR_VOLT: IC2.8 (3OUT), IC2.9 (3IN-); also elsewhere on the board

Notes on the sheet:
Openlog
Bluetooth
Temp/Humid Sensor
Mounting Holes
TVS Surge Protection
Valve Cntrl
Voltage LP Filters
Current Sensor LP Filters w/ Voltage Divider
128x64 OLED Display

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
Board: 2 copper layers, 148 parts (0 on the bottom side), 119 nets, no tracks yet.

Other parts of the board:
D308: P6KE15A-E3/54GICT-ND; DO-204AC
R123, R124: 4.7kΩ; 0805

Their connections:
AUX12V: D308.CATHODE; also elsewhere on the board
GND: D308.ANODE, R123.2, R124.1; also elsewhere on the board
